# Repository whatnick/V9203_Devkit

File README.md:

# V9203 FeatherWing Devkit
An evaluation board for Vangotech V9203 3-phase energy monitor in a
Featherwing format. It has been tested with Arduino enabled feathers
and should work with any Arduino platform with an SPI bus.

The SPI bus is 3.3v and exposed via the Feather headers and the JST
connector on the top for people wishing to use it with non-feather
format boards as host processor.

The board can be obtained on:

- [Tindie](https://www.tindie.com/products/whatnick/v9203-featherwing/)
- [OSHPark](https://oshpark.com/shared_projects/62lfzmN7)
- [Aisler](https://aisler.net/p/OBAOETDS)
- [PCBWay](https://www.pcbway.com/project/shareproject/V9203_Devkit_Featherwing.html)
  
## Board Images

### Rendered

**Top Render**

**Bottom Render**

### Assembled (with RJ45)

## Arduino Firmware
Arduino Firmware if available in [GitHub](https://github.com/whatnick/V9203_Arduino).

## Micropython Firmware
WIP

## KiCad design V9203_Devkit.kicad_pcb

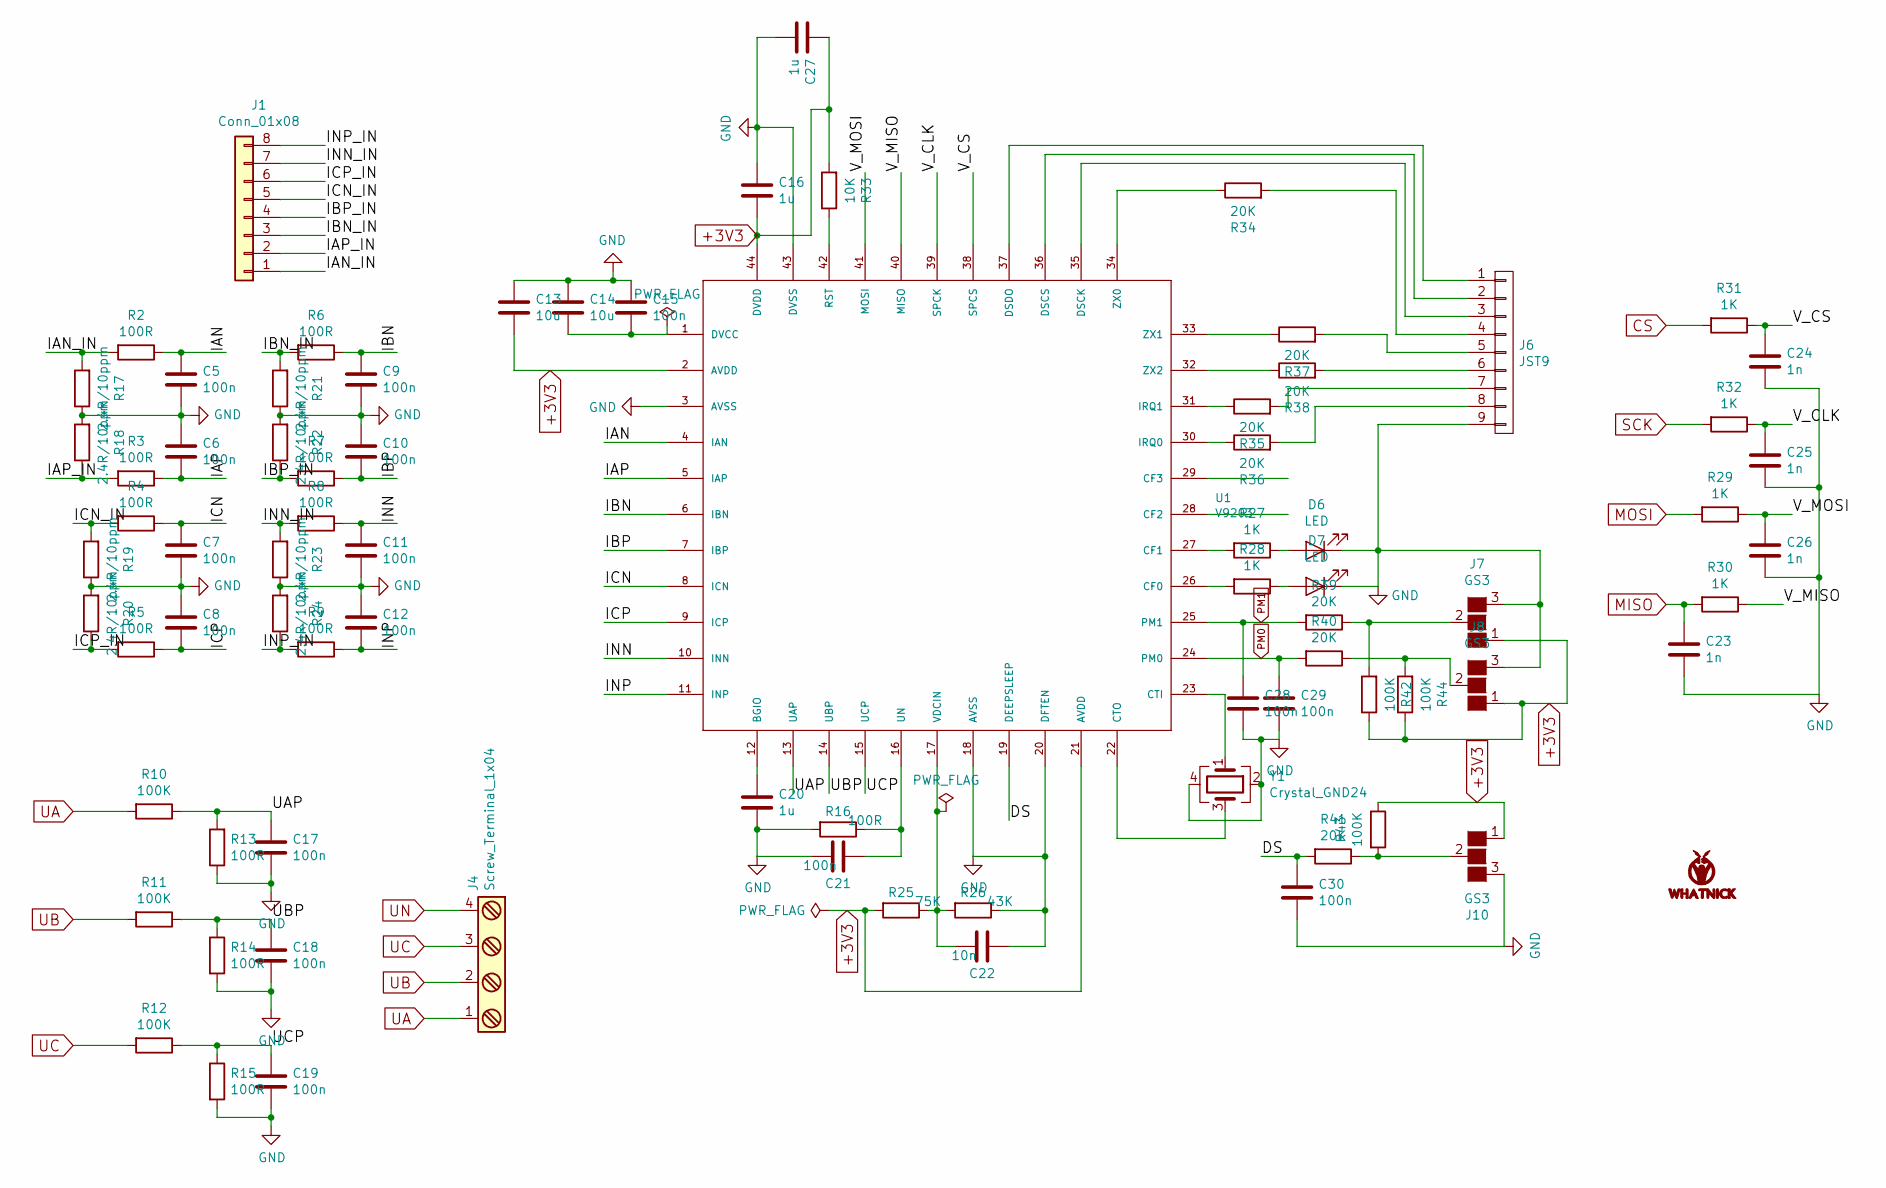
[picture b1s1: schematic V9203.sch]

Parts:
C5, C6, C7, C8, C9, C10, C11, C12, C15, C17, C18, C19, C21, C28, C29, C30: 100n; C_0402
C13, C14: 10u; CP_Tantalum_Case-A_EIA-3216-18_Reflow
C16, C20, C27: 1u; C_0402
C22: 10n; C_0402
C23, C24, C25, C26: 1n; C_0402
D6, D7: LED; LED_0603
J1: Conn_01x08; Molex_Nano-Fit_105314-xx08_2x04_P2.50mm_Horizontal
J4: Screw_Terminal_1x04; TerminalBlock_Pheonix_PT-3.5mm_4pol
J6: JST9; JST_SH_SM09B-SRSS-TB_09x1.00mm_Angled
J7, J8, J10: GS3
LOGO2: LOGO; Whatnick_logo
R2, R3, R4, R5, R6, R7, R8, R9, R13, R14, R15, R16: 100R; R_0402
R10, R11, R12: 100K; R_0603_HandSoldering
R17, R18, R19, R20, R21, R22, R23, R24: 2.4R/10ppm; R_0603
R25: 75K; R_0402
R26: 43K; R_0402
R27, R28: 1K; R_0603_HandSoldering
R29, R30, R31, R32: 1K; R_0402
R33: 10K; R_0402
R34, R35, R36, R37, R38, R39, R40, R41: 20K; R_0402
R42, R43, R44: 100K; R_0402
U1: V9203; TQFP-44_10x10mm_Pitch0.8mm
Y1: Crystal_GND24; Crystal_SMD_Abracon_ABM8G-4pin_3.2x2.5mm

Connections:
+3V3: C13.2, C16.1, C27.2, J7.1 (G1), J8.1 (G1), J10.1 (G1), R25.2, R33.2, R42.1, R43.1, R44.1, U1.2 (AVDD), U1.21 (AVDD), U1.44 (DVDD); also elsewhere on the board
/V9203/DS: C30.1, R41.2, U1.19 (DEEPSLEEP)
/V9203/IAN: C5.1, R2.1, U1.4 (IAN)
/V9203/IAN_IN: J1.1, R2.2, R17.2
/V9203/IAP: C6.2, R3.1, U1.5 (IAP)
/V9203/IAP_IN: J1.2, R3.2, R18.1
/V9203/IBN: C9.1, R6.1, U1.6 (IBN)
/V9203/IBN_IN: J1.3, R6.2, R21.2
/V9203/IBP: C10.2, R7.1, U1.7 (IBP)
/V9203/IBP_IN: J1.4, R7.2, R22.1
/V9203/ICN: C7.1, R4.1, U1.8 (ICN)
/V9203/ICN_IN: J1.5, R4.2, R19.2
/V9203/ICP: C8.2, R5.1, U1.9 (ICP)
/V9203/ICP_IN: J1.6, R5.2, R20.1
/V9203/INN: C11.1, R8.1, U1.10 (INN)
/V9203/INN_IN: J1.7, R8.2, R23.2
/V9203/INP: C12.2, R9.1, U1.11 (INP)
/V9203/INP_IN: J1.8, R9.2, R24.1
/V9203/UAP: C17.1, R10.1, R13.2, U1.13 (UAP)
/V9203/UBP: C18.1, R11.1, R14.1, U1.14 (UBP)
/V9203/UCP: C19.1, R12.1, R15.1, U1.15 (UCP)
/V9203/V_CLK: C25.1, R32.1, U1.39 (SPCK)
/V9203/V_CS: C24.1, R31.1, U1.38 (SPCS)
/V9203/V_MISO: R30.1, U1.40 (MISO)
/V9203/V_MOSI: C26.1, R29.1, U1.41 (MOSI)
CS: R31.2; also elsewhere on the board
GND: C5.2, C6.1, C7.2, C8.1, C9.2, C10.1, C11.2, C12.1, C13.1, C14.1, C15.1, C16.2, C17.2, C18.2, C19.2, C20.1, C21.2, C22.1, C23.2, C24.2, C25.2, C26.2, C27.1, C28.2, C29.2, C30.2, D6.1 (K), D7.1 (K), J4.4, J6.9, J7.3 (G3), J8.3 (G3), J10.3 (G3), R13.1, R14.2, R15.2, R16.2, R17.1, R18.2, R19.1, R20.2, R21.1, R22.2, R23.1, R24.2, R26.1, U1.3 (AVSS), U1.18 (AVSS), U1.20 (DFTEN), U1.43 (DVSS), Y1.2, Y1.4; also elsewhere on the board
MISO: C23.1, R30.2; also elsewhere on the board
MOSI: R29.2; also elsewhere on the board
unnamed: C14.2, C15.2, U1.1 (DVCC)
unnamed: C20.2, U1.12 (BGIO)
unnamed: C21.1, R16.1, U1.16 (UN)
unnamed: C22.2, R25.1, R26.2, U1.17 (VDCIN)
unnamed: D6.2 (A), R27.1
unnamed: D7.2 (A), R28.1
unnamed: J6.1, U1.37 (DSDO)
unnamed: J6.2, U1.36 (DSCS)
unnamed: J6.3, U1.35 (DSCK)
unnamed: J6.4, R34.2
unnamed: J6.5, R37.2
unnamed: J6.6, R38.2
unnamed: J6.7, R35.2
unnamed: J6.8, R36.2
unnamed: J7.2 (G2), R39.1, R42.2
unnamed: J8.2 (G2), R40.1, R44.2
unnamed: J10.2 (G2), R41.1, R43.2
unnamed: R27.2, U1.27 (CF1)
unnamed: R28.2, U1.26 (CF0)
unnamed: R33.1, U1.42 (RST)
unnamed: R34.1, U1.34 (ZX0)
unnamed: R35.1, U1.31 (IRQ1)
unnamed: R36.1, U1.30 (IRQ0)
unnamed: R37.1, U1.33 (ZX1)
unnamed: R38.1, U1.32 (ZX2)
unnamed: U1.22 (CTO), Y1.3
unnamed: U1.23 (CTI), Y1.1
PM0: C29.1, R40.2, U1.24 (PM0)
PM1: C28.1, R39.2, U1.25 (PM1)
SCK: R32.2; also elsewhere on the board
UA: J4.1, R10.2; also elsewhere on the board
UB: J4.2, R11.2; also elsewhere on the board
UC: J4.3, R12.2; also elsewhere on the board

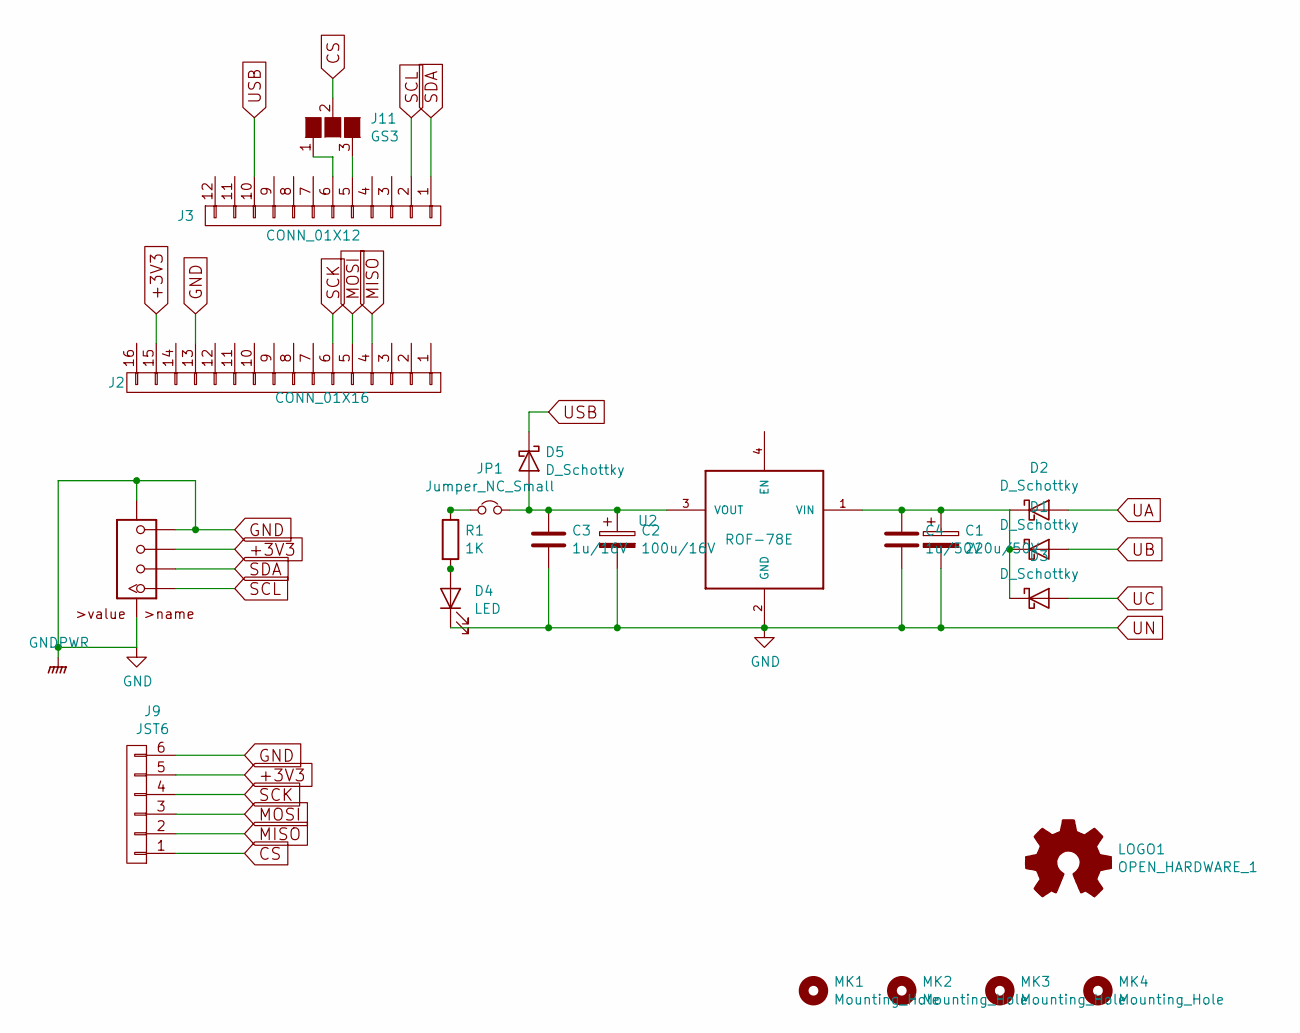
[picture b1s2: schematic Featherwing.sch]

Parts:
C1: 220u/50V; CP_Elec_8x10
C2: 100u/16V; CP_Elec_5x5.8
C3: 1u/16V; C_0603
C4: 1u/50V; C_0603
D1, D2, D3: D_Schottky; D_SMA_Standard
D4: LED; LED_0603
D5: D_Schottky; D_SOD-123
J2: CONN_01X16; Socket_Strip_Straight_1x16_Pitch2.54mm
J3: CONN_01X12; Socket_Strip_Straight_1x12_Pitch2.54mm
J5: GROVE-CONNECTOR-SMD-90D(4+2P-2.0); HW4-SMD-2.0-90D
J9: JST6; JST_SH_SM06B-SRSS-TB_06x1.00mm_Angled
J11: GS3
JP1: Jumper_NC_Small; GS2
LOGO1: OPEN_HARDWARE_1; OSHW-Logo2_7.3x6mm_SilkScreen
MK1, MK2, MK3, MK4: Mounting_Hole; MountingHole_2.2mm_M2
R1: 1K; R_0603_HandSoldering
U2: ROF-78E; SMD-4

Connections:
+3V3: J2.15, J5.3, J9.5; also elsewhere on the board
CS: J9.1, J11.2 (G2); also elsewhere on the board
GND: C1.2, C2.2, C3.2, C4.2, D4.1 (K), J2.13, J5.4, J5.SS1, J5.SS2, J9.6, U2.2 (GND); also elsewhere on the board
MISO: J2.4, J9.2; also elsewhere on the board
MOSI: J2.5, J9.3; also elsewhere on the board
unnamed: C1.1, C4.1, D1.1 (K), D2.1 (K), D3.1 (K), U2.1 (VIN)
unnamed: C2.1, C3.1, D5.2 (A), JP1.2, U2.3 (VOUT)
unnamed: D4.2 (A), R1.2
unnamed: J3.6, J11.1 (G1)
unnamed: J3.5, J11.3 (G3)
unnamed: JP1.1, R1.1
SCK: J2.6, J9.4; also elsewhere on the board
SCL: J3.2, J5.1
SDA: J3.1, J5.2
UA: D2.2 (A); also elsewhere on the board
UB: D1.2 (A); also elsewhere on the board
UC: D3.2 (A); also elsewhere on the board
USB: D5.1 (K), J3.10

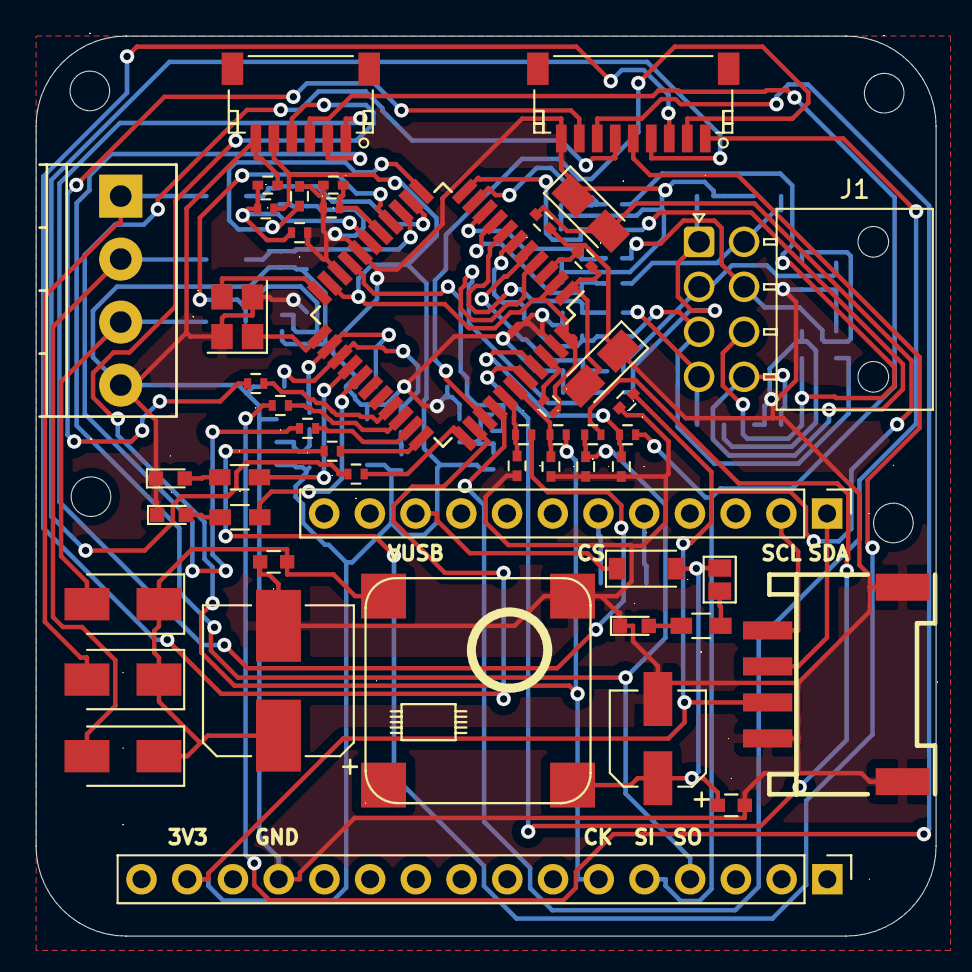
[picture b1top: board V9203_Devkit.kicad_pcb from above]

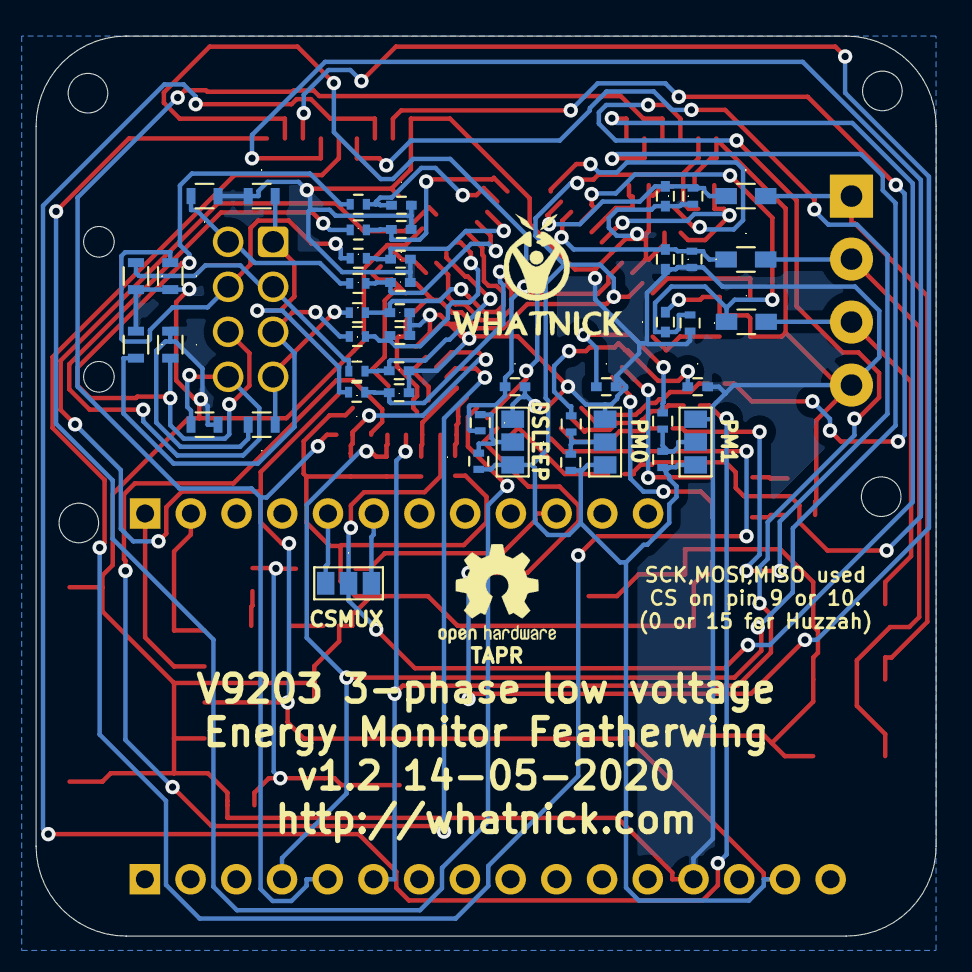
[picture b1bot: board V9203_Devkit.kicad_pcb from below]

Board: 2 copper layers, 50.0 x 50.0 mm, 102 parts (48 on the bottom side), 71 nets.

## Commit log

2017-04-04 Initial import
2017-04-17 Added more parts to featherwing
2017-04-23 Laid out most parts within PCB bounds
2017-04-24 Neaten up parts layout
2017-04-25 Added JST footprints, mounting holes and logos
2017-04-25 Blanked all test
2017-04-25 Blanked all text
2017-04-25 Added more signals to JST connector including DMA
2017-04-26 Added Molex step file
2017-04-26 Flipped connectors
2017-04-28 More connector models
2017-04-29 Added logos
2017-04-29 Added PM0,1 and Deepsleep circuits
2017-04-30 Laid out components so far pending ERC,routing and review
2017-04-30 Ran ERC and updated pcb
2017-04-30 Set up for Freeroute
2017-05-01 Freeroute run
2017-05-01 Changed crystal and diode models
2017-05-02 With CS mux, improve silk screen in next rev
2017-05-02 Added ground plane
2017-05-02 Added silk screen markers
2017-05-02 Added silk screen for pins
2017-05-05 Added component values from reference design
2017-05-06 Started adding part numbers
2017-05-07 Added more part numbers
2017-05-08 More part numbers
2017-05-09 JST parts
2017-06-04 Fixed a ground connection
2017-06-04 Added app notes
2017-06-05 Bump version
2017-06-05 Moved docs
2020-05-01 Migrate to kicad 5
2020-05-07 Start a README
2020-05-07 Add gitignore
2020-05-07 Why was I adding README to Molex ?
2020-05-07 Link to Arduino Firmware
2020-05-10 Add iBOM
2020-05-14 New data and gerbers
2020-05-14 Add gerber zip to ignore
2020-05-14 Add Bom Excel
2020-05-16 Add more images and README
